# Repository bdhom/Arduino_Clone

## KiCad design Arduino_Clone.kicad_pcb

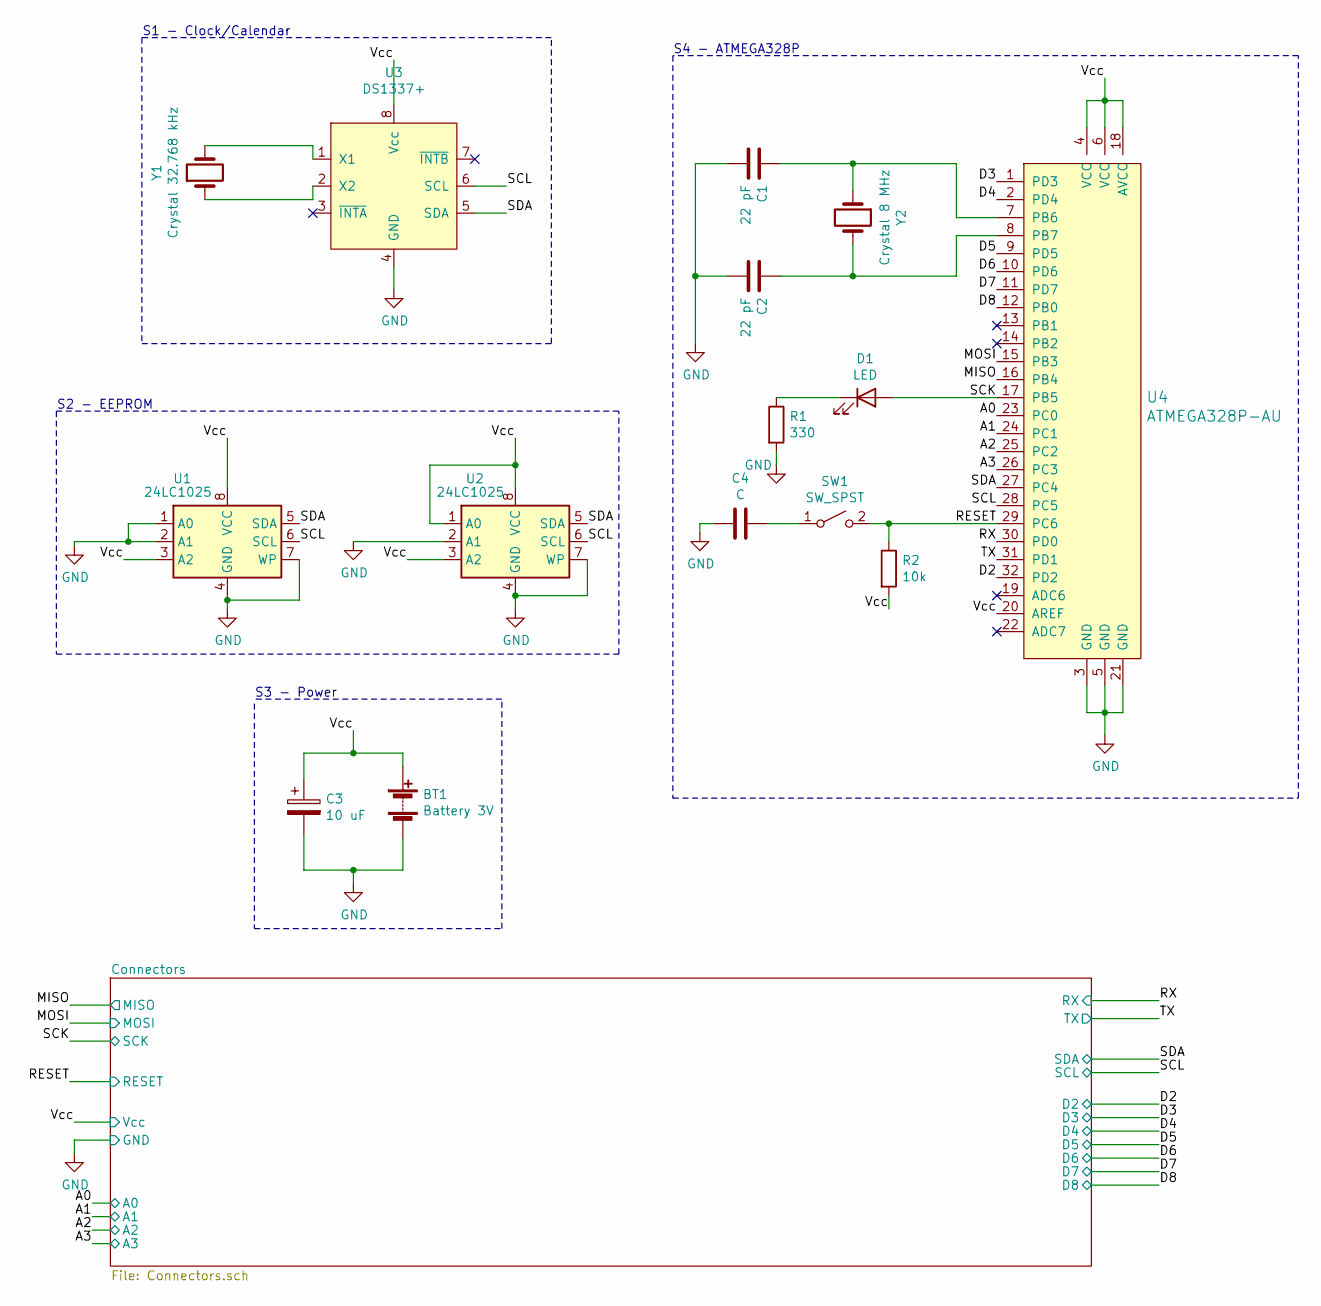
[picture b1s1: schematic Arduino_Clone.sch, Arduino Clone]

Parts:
BT1: Battery 3V; PinHeader_1x02_P2.54mm_Vertical
C1, C2: 22 pF; C_0805_2012Metric_Pad1.18x1.45mm_HandSolder
C3: 10 uF; C_0805_2012Metric_Pad1.18x1.45mm_HandSolder
C4: C; C_0805_2012Metric_Pad1.18x1.45mm_HandSolder
D1: LED; LED_0805_2012Metric_Pad1.15x1.40mm_HandSolder
R1: 330; R_0805_2012Metric_Pad1.20x1.40mm_HandSolder
R2: 10k; R_0805_2012Metric_Pad1.20x1.40mm_HandSolder
SW1: SW_SPST; SPST_SW
U1, U2: 24LC1025; SOIC-8_3.9mmX4.9mm
U3: DS1337+; SOIC-8_3.9x4.9mm_P1.27mm
U4: ATMEGA328P-AU; TQFP-32_7x7mm; MPN ATMEGA328P-AU; Digi-Key_PN ATMEGA328P-AU-ND
Y1: Crystal 32.768 kHz; Crystal_SMD_MicroCrystal_CC7V-T1A-2Pin_3.2x1.5mm_HandSolder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
Y2: Crystal 8 MHz; Crystal_SMD_5032-2Pin_5.0x3.2mm_HandSoldering

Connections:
/A0: U4.23 (PC0); also elsewhere on the board
/A1: U4.24 (PC1); also elsewhere on the board
/A2: U4.25 (PC2); also elsewhere on the board
/A3: U4.26 (PC3); also elsewhere on the board
/D2: U4.32 (PD2); also elsewhere on the board
/D3: U4.1 (PD3); also elsewhere on the board
/D4: U4.2 (PD4); also elsewhere on the board
/D5: U4.9 (PD5); also elsewhere on the board
/D6: U4.10 (PD6); also elsewhere on the board
/D7: U4.11 (PD7); also elsewhere on the board
/D8: U4.12 (PB0); also elsewhere on the board
/MISO: U4.16 (PB4); also elsewhere on the board
/MOSI: U4.15 (PB3); also elsewhere on the board
/RESET: R2.1, SW1.2 (B), U4.29 (PC6); also elsewhere on the board
/RX: U4.30 (PD0); also elsewhere on the board
/SDA: U1.5 (SDA), U2.5 (SDA), U3.5 (SDA), U4.27 (PC4); also elsewhere on the board
/TX: U4.31 (PD1); also elsewhere on the board
/Vcc: BT1.1 (+), C3.1, R2.2, U1.3 (A2), U1.8 (VCC), U2.1 (A0), U2.3 (A2), U2.8 (VCC), U3.8 (Vcc), U4.4 (VCC), U4.6 (VCC), U4.18 (AVCC), U4.20 (AREF); also elsewhere on the board
GND: BT1.2 (-), C1.2, C2.2, C3.2, C4.2, R1.2, U1.1 (A0), U1.2 (A1), U1.4 (GND), U1.7 (WP), U2.2 (A1), U2.4 (GND), U2.7 (WP), U3.4 (GND), U4.3 (GND), U4.5 (GND), U4.21 (GND); also elsewhere on the board
unnamed: C1.1, U4.7 (PB6), Y2.1
unnamed: C2.1, U4.8 (PB7), Y2.2
unnamed: C4.1, SW1.1 (A)
unnamed: D1.1 (K), R1.1
unnamed: U3.1 (X1), Y1.2
unnamed: U3.2 (X2), Y1.1

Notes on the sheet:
S1 - Clock/Calendar
S2 - EEPROM
S3 - Power
S4 - ATMEGA328P

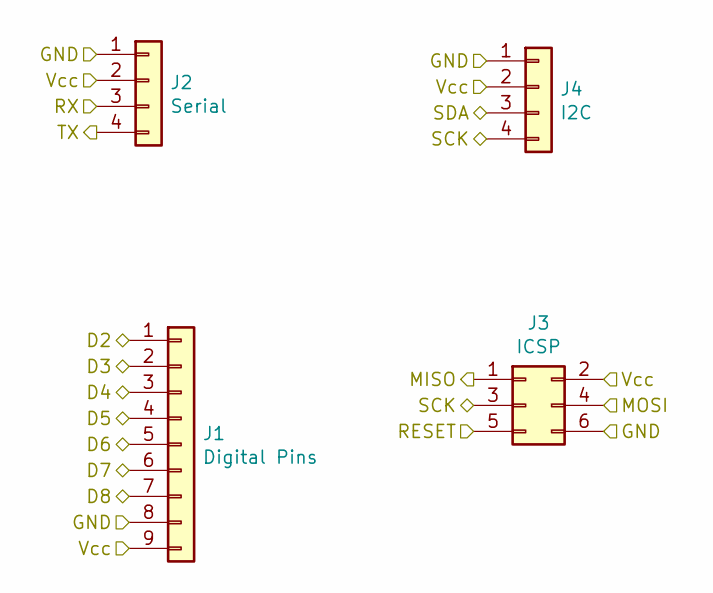
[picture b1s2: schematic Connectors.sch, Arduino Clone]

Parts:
J1: Digital Pins; PinSocket_1x09_P2.54mm_Vertical
J2: Serial; PinSocket_1x04_P2.54mm_Vertical
J3: ICSP; PinSocket_2x03_P2.54mm_Vertical
J4: I2C; PinSocket_1x04_P2.54mm_Vertical

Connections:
/D2: J1.1; also elsewhere on the board
/D3: J1.2; also elsewhere on the board
/D4: J1.3; also elsewhere on the board
/D5: J1.4; also elsewhere on the board
/D6: J1.5; also elsewhere on the board
/D7: J1.6; also elsewhere on the board
/D8: J1.7; also elsewhere on the board
/MISO: J3.1; also elsewhere on the board
/MOSI: J3.4; also elsewhere on the board
/RESET: J3.5; also elsewhere on the board
/RX: J2.3; also elsewhere on the board
/SDA: J4.3; also elsewhere on the board
/TX: J2.4; also elsewhere on the board
/Vcc: J1.9, J2.2, J3.2, J4.2; also elsewhere on the board
GND: J1.8, J2.1, J3.6, J4.1; also elsewhere on the board

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
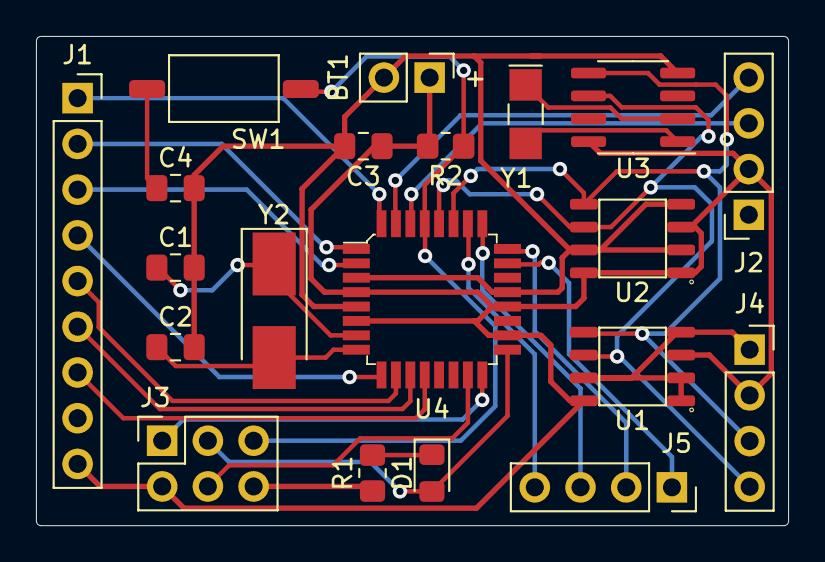
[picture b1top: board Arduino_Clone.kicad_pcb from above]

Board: 2 copper layers, 41.8 x 27.2 mm, 20 parts (0 on the bottom side), 27 nets.

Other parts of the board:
J5: Analog Pins; PinSocket_1x04_P2.54mm_Vertical

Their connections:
/A0: J5.1; also elsewhere on the board
/A1: J5.2; also elsewhere on the board
/A2: J5.3; also elsewhere on the board
/A3: J5.4; also elsewhere on the board

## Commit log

2021-01-31 Setup title block for schematic.
2021-01-31 Added new child sheet.
2021-01-31 Added symbols to new sheet.
2021-01-31 Added custom clock IC symbol.
2021-01-31 Added footprint associations.
2021-01-31 Added wiring in connectors sheet.
2021-02-04 Added more necessary components. Corrected winrings. Generated netlist.
2021-02-05 First version of placements on PCB layout
2021-02-06 Second version of component placement on pcb layout.
2021-02-06 Finished PCB Layout.
